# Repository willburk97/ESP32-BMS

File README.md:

# ESP32-BMS
Single ESP32 monitoring and balancing multiple cell Li-Ion battery.

For each cell, to enable discharging, the ESP32 drives an opto-coupler (P521) with the digital output and the opto-coupler is driving the discharge mosfet(IRFZ44N) /resistor(16ohm,3W) across each cell. This'll be duplicatable across any number of cells (given the ESP32 has enough analog inputs and digital outputs. I'm using it for a 4 cell BMS/monitor which is using Adafruit io for trending/remote monitoring. The RJ11 port is to connect it to an Inverter. This is NOW coded in. I wasn't able to test the newer design with my old Kisae Inverter but the circuit in my original BMS worked fine (The single Arduino with a ESP8266-01 BMS).  

Note:  I added an I2C port to easily allow for adding components (like maybe an LCD/OLED display).

Ordered PCB and succesfully tested it (before I added the mounting holes and the wider traces.)   Worked great (didn't test i2c or rj11 port.)

My Kisae SW1220 inverter died in a lightning strike, but if you have one I think the schematic/board need to be changed to have Battery+ going to the optocoupler and the other leg going to the RJ11 port. (The wires on the opto-coupler will have to be reversed of course.)

My replacement inverter, a Go-Power GP-SW2000-12, has a remote input (Gnd, Enab, !Enab). I was able to use the schematic/board as is and simply connect the !Enab input on the inverter directly to the opto-coupler connection at the RJ11 port. (Which gets grounded when the digital output from the ESP32 turns on.)

Note: The Kisae inverter used a momentary Battery+ signal to turn the inverter on or off (change it from one state to the other).  The Go Power inverter requires a constant input signal (either battery+ or Gnd depending on the input you use) in order to be powered on. (Enab requires Batt+, !Enab requires Gnd, pick one to use.) The current code works with the Go Power Inverter.

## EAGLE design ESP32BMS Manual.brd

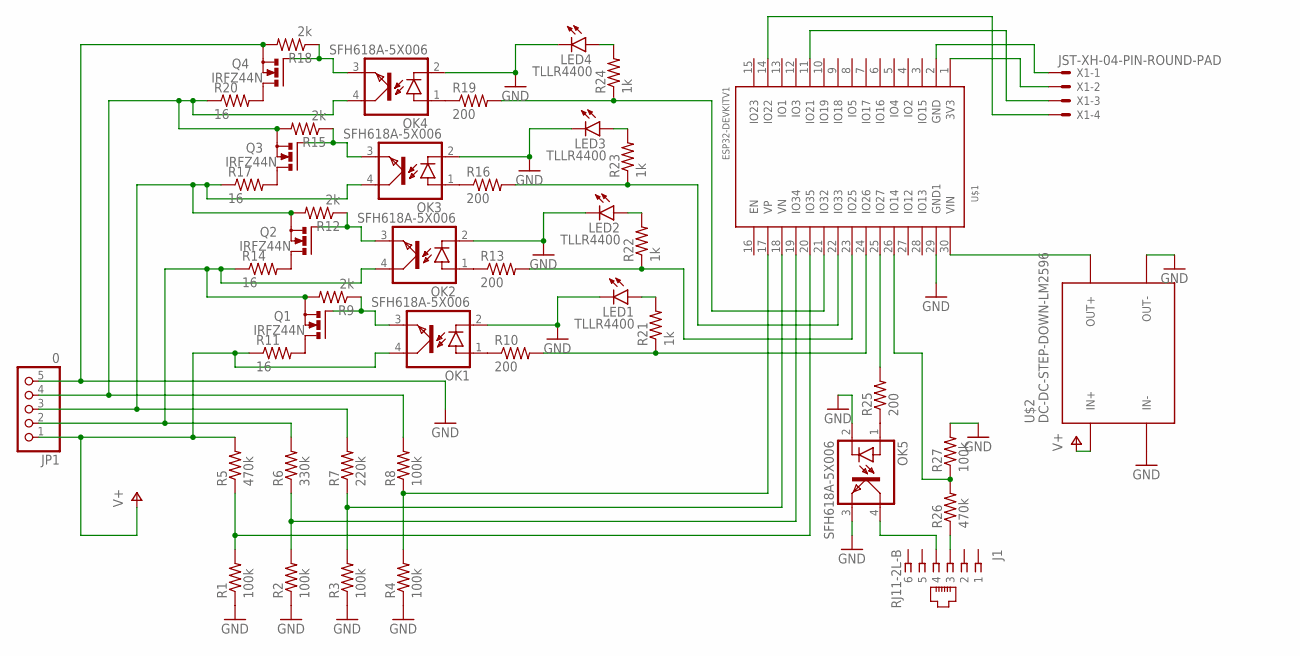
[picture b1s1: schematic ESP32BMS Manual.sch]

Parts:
J1: RJ11-2L-B; RJ11-NO_SHIELD
JP1: 0; 1X05
LED1, LED2, LED3, LED4: TLLR4400; LED3MM
OK1, OK2, OK3, OK4, OK5: SFH618A-5X006; DIP4-400
Q1, Q2, Q3, Q4: IRFZ44N; TO220BV
R1, R2, R3, R4, R8, R27: 100k; 0204/7
R5, R26: 470k; 0204/7
R6: 330k; 0204/7
R7: 220k; 0204/7
R9, R12, R15, R18: 2k; 0204/7
R10, R13, R16, R19, R25: 200; 0204/7
R11, R14, R17, R20: 16; 0414V
R21, R22, R23, R24: 1k; 0204/7
U$1: ESP32DEVKITV1; ESP32-DEVKITV1
U$2: DC-DC-STEP-DOWN-LM2596
X1: JST-XH-04-PIN-ROUND-PAD; JST-XH-04-PACKAGE-ROUND-PAD

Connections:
GND: JP1.5, LED1.K (C), LED2.K (C), LED3.K (C), LED4.K (C), OK1.2 (C), OK2.2 (C), OK3.2 (C), OK4.2 (C), OK5.2 (C), OK5.3 (EMIT), Q4.S, R1.1, R2.1, R3.1, R4.1, R18.2, R27.2, U$1.29 (GND1), U$2.IN-, U$2.OUT-
unnamed: R4.2, R8.1, U$1.17 (VP)
unnamed: R3.2, R7.1, U$1.18 (VN)
unnamed: R2.2, R6.1, U$1.19 (IO34)
unnamed: R1.2, R5.1, U$1.20 (IO35)
unnamed: LED1.A, R21.2
unnamed: JP1.2, OK2.4 (COL), Q1.S, R6.2, R9.2, R14.1
unnamed: JP1.3, OK3.4 (COL), Q2.S, R7.2, R12.2, R17.1
unnamed: JP1.4, OK4.4 (COL), Q3.S, R8.2, R15.2, R20.1
unnamed: OK1.1 (A), R10.1
unnamed: R19.2, R24.1, U$1.21 (IO32)
unnamed: OK2.1 (A), R13.1
unnamed: R16.2, R23.1, U$1.22 (IO33)
unnamed: R13.2, R22.1, U$1.23 (IO25)
unnamed: Q1.D, R11.2
unnamed: OK1.3 (EMIT), Q1.G, R9.1
unnamed: R10.2, R21.1, U$1.24 (IO26)
unnamed: Q2.D, R14.2
unnamed: OK2.3 (EMIT), Q2.G, R12.1
unnamed: U$1.30 (VIN), U$2.OUT+
unnamed: OK3.1 (A), R16.1
unnamed: LED2.A, R22.2
unnamed: Q3.D, R17.2
unnamed: OK3.3 (EMIT), Q3.G, R15.1
unnamed: LED3.A, R23.2
unnamed: OK4.1 (A), R19.1
unnamed: LED4.A, R24.2
unnamed: Q4.D, R20.2
unnamed: OK4.3 (EMIT), Q4.G, R18.1
unnamed: OK5.1 (A), R25.1
unnamed: R26.2, R27.1, U$1.26 (IO14)
unnamed: R25.2, U$1.25 (IO27)
unnamed: J1.3, R26.1
unnamed: J1.4, OK5.4 (COL)
unnamed: U$1.1 (3V3), X1.2
unnamed: U$1.2 (GND), X1.1
unnamed: U$1.11 (IO21), X1.3
unnamed: U$1.14 (IO22), X1.4
V+: JP1.1, OK1.4 (COL), R5.2, R11.1, U$2.IN+

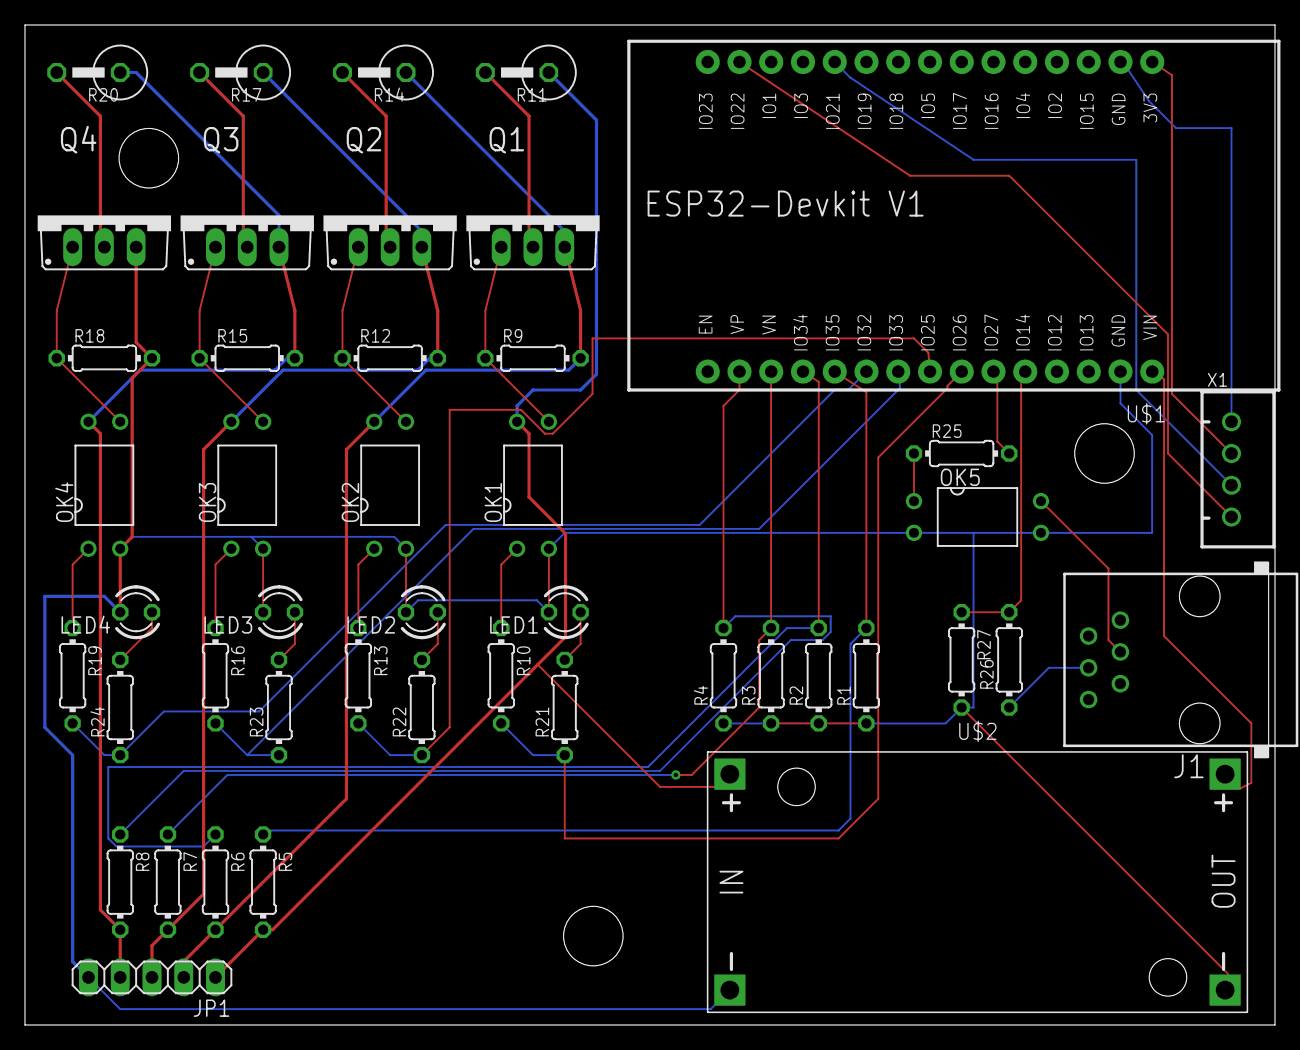
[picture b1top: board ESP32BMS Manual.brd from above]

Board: 2 copper layers, 100.0 x 80.0 mm, 45 parts (0 on the bottom side), 39 nets.

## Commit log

2020-07-30 Adding Schematics
    The mosfets and the optocouplers listed are not what I used (I couldn't find them in Eagle). I used an IRZF44N mosfet and P521 Opto-Coupler. The resistors values are correct but the part numbers are 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
2020-07-30 Fixed polarity on batteries in schematics.
2020-08-15 Added mounting holes and widened discharge paths/traces.
2020-08-17 Added Inverter Code
    Added Basic Inverter control code... My go-power sw2000-12 inverter has a remote input which is connected directly to the opto-coupler output (at the RJ11 port). Open = inverter off, grounded = inver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
2021-10-12 Add photo of functional board

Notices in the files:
parts and their libraries:
diy-modules: Released under the Creative Commons Attribution 4.0 International License: http://creativecommons.org/licenses/by/4.0
